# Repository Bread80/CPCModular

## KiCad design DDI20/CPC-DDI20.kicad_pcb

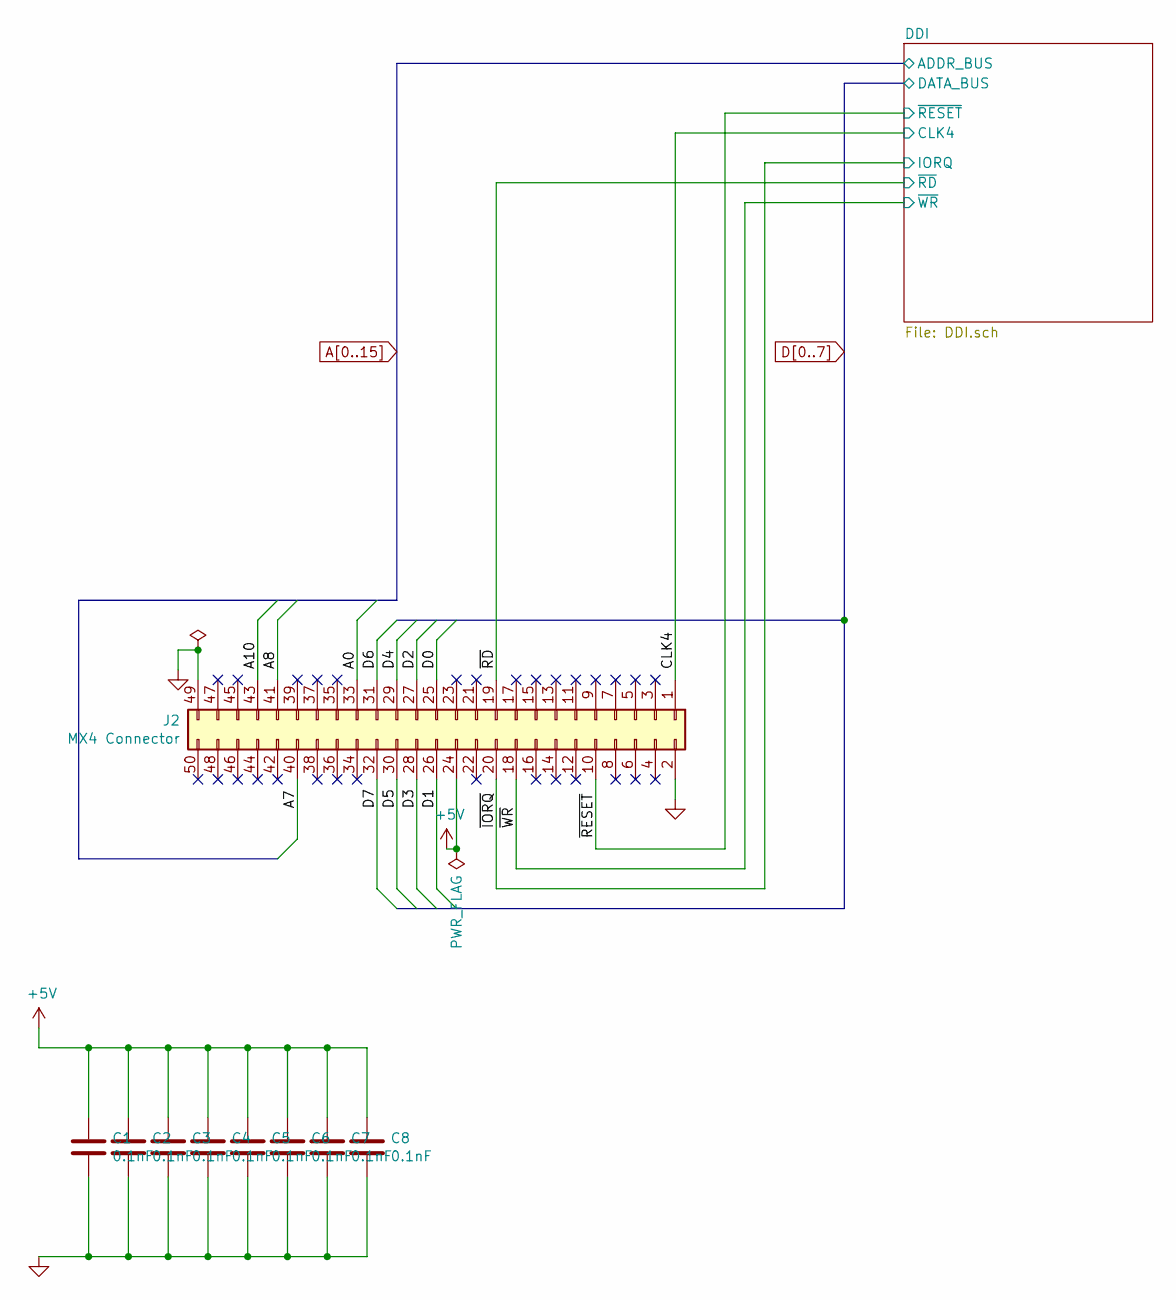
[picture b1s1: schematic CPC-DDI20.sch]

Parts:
C1, C2, C3, C4, C5, C6, C7, C8: 0.1nF; C_Disc_D3.0mm_W2.0mm_P2.50mm
J2: MX4 Connector; IDC-Header_2x25_P2.54mm_Horizontal

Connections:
+5V: C1.1, C2.1, C3.1, C4.1, C5.1, C6.1, C7.1, C8.1, J2.24; also elsewhere on the board
/CLK4: J2.1; also elsewhere on the board
/~IORQ: J2.20; also elsewhere on the board
/~RD: J2.19; also elsewhere on the board
/~RESET: J2.10; also elsewhere on the board
/~WR: J2.18; also elsewhere on the board
A0: J2.33; also elsewhere on the board
A7: J2.40; also elsewhere on the board
A8: J2.41; also elsewhere on the board
A10: J2.43; also elsewhere on the board
D0: J2.25; also elsewhere on the board
D1: J2.26; also elsewhere on the board
D2: J2.27; also elsewhere on the board
D3: J2.28; also elsewhere on the board
D4: J2.29; also elsewhere on the board
D5: J2.30; also elsewhere on the board
D6: J2.31; also elsewhere on the board
D7: J2.32; also elsewhere on the board
GND: C1.2, C2.2, C3.2, C4.2, C5.2, C6.2, C7.2, C8.2, J2.2, J2.49; also elsewhere on the board

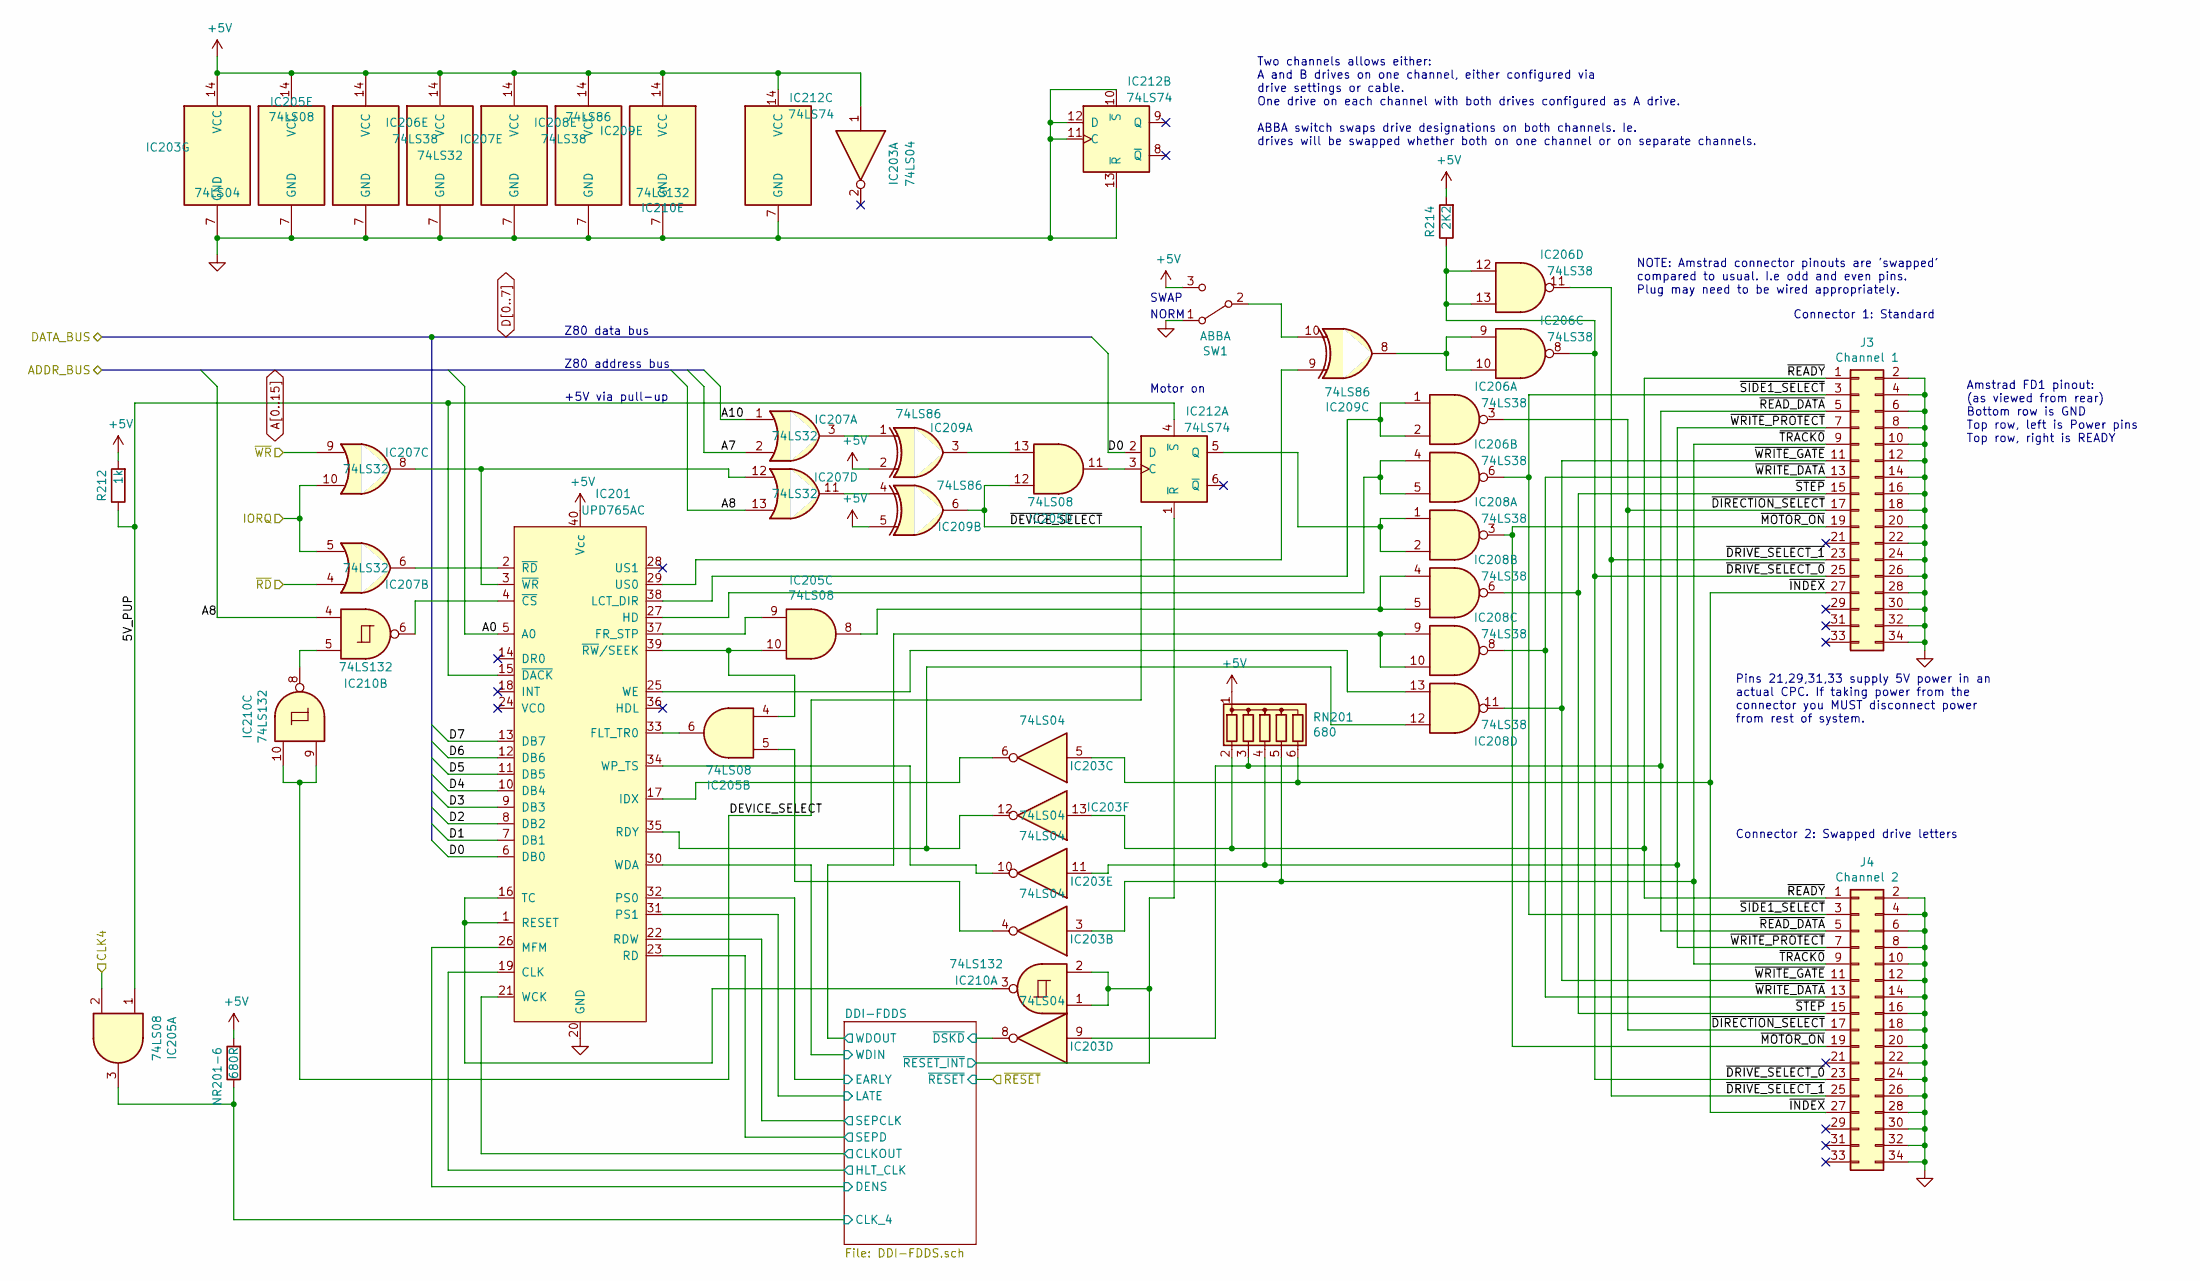
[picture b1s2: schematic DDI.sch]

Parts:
IC201: UPD765AC; DIP-40_W15.24mm_Socket
IC203: 74LS04; DIP-14_W7.62mm_Socket
IC205: 74LS08; DIP-14_W7.62mm_Socket
IC206, IC208: 74LS38; DIP-14_W7.62mm_Socket
IC207: 74LS32; DIP-14_W7.62mm_Socket
IC209: 74LS86; DIP-14_W7.62mm_Socket
IC210: 74LS132; DIP-14_W7.62mm_Socket
IC212: 74LS74; DIP-14_W7.62mm_Socket
J3: Channel 1; IDC-Header_2x17_P2.54mm_Vertical
J4: Channel 2; IDC-Header_2x17_P2.54mm_Vertical
NR201-6: 680R; R_Axial_DIN0207_L6.3mm_D2.5mm_P7.62mm_Horizontal
R212: 1k; R_Axial_DIN0207_L6.3mm_D2.5mm_P7.62mm_Horizontal
R214: 2K2; R_Axial_DIN0207_L6.3mm_D2.5mm_P7.62mm_Horizontal
RN201: 680; R_Array_SIP6
SW1: ABBA; SW_CuK_OS102011MA1QN1_SPDT_Angled

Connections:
+5V: IC201.40 (Vcc), IC203.1, IC203.14 (VCC), IC205.14 (VCC), IC206.14 (VCC), IC207.14 (VCC), IC208.14 (VCC), IC209.2, IC209.5, IC209.14 (VCC), IC210.14 (VCC), IC212.14 (VCC), NR201-6.2, R212.2, R214.2, RN201.1 (common), SW1.3 (C); also elsewhere on the board
/CLK4: IC205.2; also elsewhere on the board
/DDI/5V_PUP: IC201.15 (~DACK), IC205.1, IC212.4 (~S), R212.1
/DDI/DDI-FDDS/CLKOUT: IC201.21 (WCK); also elsewhere on the board
/DDI/DDI-FDDS/CLK_4: IC205.3, NR201-6.1; also elsewhere on the board
/DDI/DDI-FDDS/DENS: IC201.26 (MFM); also elsewhere on the board
/DDI/DDI-FDDS/EARLY: IC201.32 (PS0); also elsewhere on the board
/DDI/DDI-FDDS/HLT_CLK: IC201.19 (CLK); also elsewhere on the board
/DDI/DDI-FDDS/LATE: IC201.31 (PS1); also elsewhere on the board
/DDI/DDI-FDDS/SEPCLK: IC201.22 (RDW); also elsewhere on the board
/DDI/DDI-FDDS/SEPD: IC201.23 (RD); also elsewhere on the board
/DDI/DDI-FDDS/WDIN: IC201.30 (WDA); also elsewhere on the board
/DDI/DDI-FDDS/WDOUT: IC208.9, IC208.10; also elsewhere on the board
/DDI/DDI-FDDS/~DSKD: IC203.8; also elsewhere on the board
/DDI/DDI-FDDS/~RESET_INT: IC210.1, IC210.2, IC212.1 (~R); also elsewhere on the board
/DDI/DEVICE_SELECT: IC205.12, IC209.6, IC210.9, IC210.10
/DDI/~DIRECTION_SELECT: IC206.3, J3.17, J4.17
/DDI/~DRIVE_SELECT_0: IC206.8, IC206.12, IC206.13, J3.25, J4.23, R214.1
/DDI/~DRIVE_SELECT_1: IC206.11, J3.23, J4.25
/DDI/~INDEX: IC203.5, J3.27, J4.27, RN201.6 (R5)
/DDI/~MOTOR_ON: IC208.3, J3.19, J4.19
/DDI/~READY: IC203.13, J3.1, J4.1, RN201.2 (R1)
/DDI/~READ_DATA: IC203.9, J3.5, J4.5, RN201.3 (R2)
/DDI/~SIDE1_SELECT: IC206.6, J3.3, J4.3
/DDI/~STEP: IC208.6, J3.15, J4.15
/DDI/~TRACK0: IC203.3, J3.9, J4.9, RN201.5 (R4)
/DDI/~WRITE_DATA: IC208.8, J3.13, J4.13
/DDI/~WRITE_GATE: IC208.11, J3.11, J4.11
/DDI/~WRITE_PROTECT: IC203.11, J3.7, J4.7, RN201.4 (R3)
/~IORQ: IC207.5, IC207.10; also elsewhere on the board
/~RD: IC207.4; also elsewhere on the board
/~WR: IC207.9; also elsewhere on the board
A0: IC201.5 (A0); also elsewhere on the board
A7: IC207.2; also elsewhere on the board
A8: IC207.13, IC210.4; also elsewhere on the board
A10: IC207.1; also elsewhere on the board
D0: IC201.6 (DB0), IC212.2 (D); also elsewhere on the board
D1: IC201.7 (DB1); also elsewhere on the board
D2: IC201.8 (DB2); also elsewhere on the board
D3: IC201.9 (DB3); also elsewhere on the board
D4: IC201.10 (DB4); also elsewhere on the board
D5: IC201.11 (DB5); also elsewhere on the board
D6: IC201.12 (DB6); also elsewhere on the board
D7: IC201.13 (DB7); also elsewhere on the board
GND: IC201.20 (GND), IC203.7 (GND), IC205.7 (GND), IC206.7 (GND), IC207.7 (GND), IC208.7 (GND), IC209.7 (GND), IC210.7 (GND), IC212.7 (GND), IC212.10 (~S), IC212.11 (C), IC212.12 (D), IC212.13 (~R), J3.2, J3.4, J3.6, J3.8, J3.10, J3.12, J3.14, J3.16, J3.18, J3.20, J3.22, J3.24, J3.26, J3.28, J3.30, J3.32, J3.34, J4.2, J4.4, J4.6, J4.8, J4.10, J4.12, J4.14, J4.16, J4.18, J4.20, J4.22, J4.24, J4.26, J4.28, J4.30, J4.32, J4.34, SW1.1 (A); also elsewhere on the board
unnamed: IC201.1 (RESET), IC201.16 (TC), IC210.3
unnamed: IC201.2 (~RD), IC207.6
unnamed: IC201.3 (~WR), IC207.8, IC207.12
unnamed: IC201.4 (~CS), IC210.6
unnamed: IC201.17 (IDX), IC203.6
unnamed: IC201.25 (WE), IC208.13
unnamed: IC201.27 (HD), IC206.4, IC206.5
unnamed: IC201.29 (US0), IC209.9
unnamed: IC201.33 (FLT_TR0), IC205.6
unnamed: IC201.34 (WP_TS), IC203.10
unnamed: IC201.35 (RDY), IC203.12, IC208.12
unnamed: IC201.37 (FR_STP), IC205.9
unnamed: IC201.38 (LCT_DIR), IC206.1, IC206.2
unnamed: IC201.39 (~RW~/SEEK), IC205.4, IC205.10
unnamed: IC203.4, IC205.5
unnamed: IC205.8, IC208.4, IC208.5
unnamed: IC205.11, IC212.3 (C)
unnamed: IC205.13, IC209.3
unnamed: IC206.9, IC206.10, IC209.8
unnamed: IC207.3, IC209.1
unnamed: IC207.11, IC209.4
unnamed: IC208.1, IC208.2, IC212.5 (Q)
unnamed: IC209.10, SW1.2 (B)
unnamed: IC210.5, IC210.8

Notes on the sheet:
Motor on
Z80 data bus
Z80 address bus
+5V via pull-up
Pins 21,29,31,33 supply 5V power in an actual CPC. If taking power from the connector you MUST disconnect power from rest of system.
Connector 1: Standard
Connector 2: Swapped drive letters
NORM
SWAP
Two channels allows either: A and B drives on one channel, either configured via drive settings or cable. One drive on each channel with both drives configured as A drive. ABBA switch swaps drive designations on both channels. Ie. drives will be swapped whether both on one channel or on separate ch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
NOTE: Amstrad connector pinouts are 'swapped' compared to usual. I.e odd and even pins. Plug may need to be wired appropriately.
Amstrad FD1 pinout: (as viewed from rear) Bottom row is GND Top row, left is Power pins Top row, right is READY

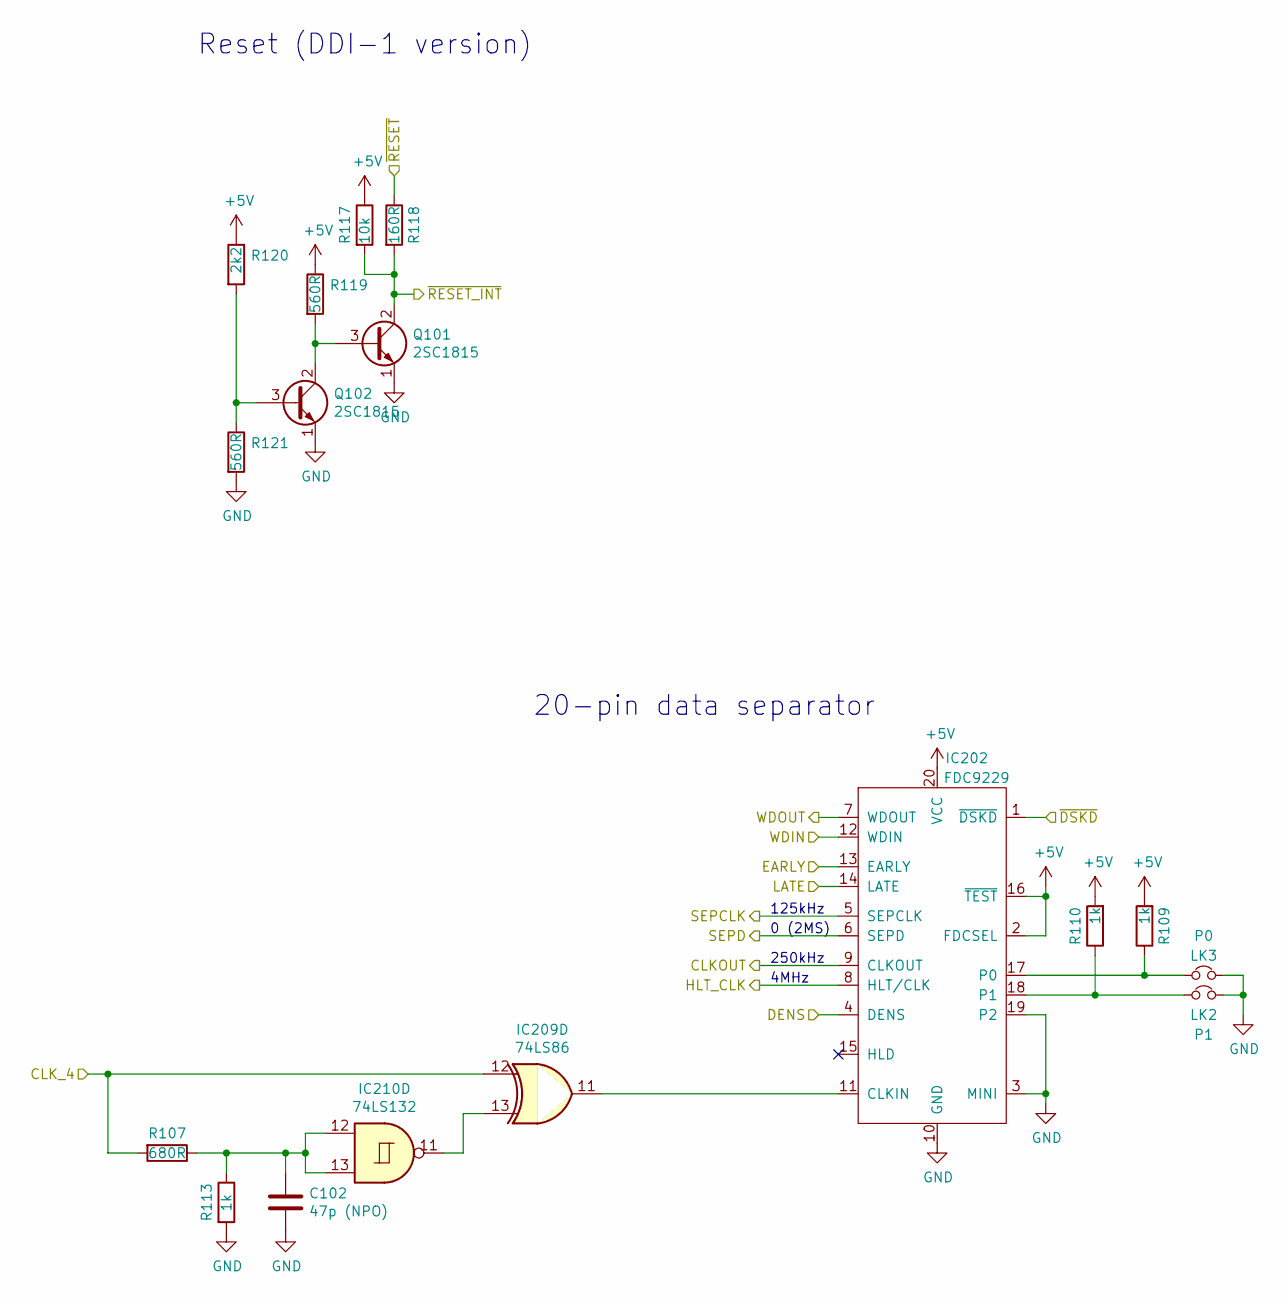
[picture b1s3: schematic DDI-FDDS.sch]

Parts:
C102: 47p (NPO); C_Disc_D3.0mm_W2.0mm_P2.50mm
IC202: FDC9229; DIP-20_W7.62mm_Socket
IC209: 74LS86; DIP-14_W7.62mm_Socket
IC210: 74LS132; DIP-14_W7.62mm_Socket
LK2: P1; SolderJumper-2_P1.3mm_Bridged_RoundedPad1.0x1.5mm
LK3: P0; SolderJumper-2_P1.3mm_Bridged_RoundedPad1.0x1.5mm
Q101, Q102: 2SC1815; TO-92_HandSolder
R107: 680R; R_Axial_DIN0207_L6.3mm_D2.5mm_P7.62mm_Horizontal
R109, R110, R113: 1k; R_Axial_DIN0207_L6.3mm_D2.5mm_P7.62mm_Horizontal
R117: 10k; R_Axial_DIN0207_L6.3mm_D2.5mm_P7.62mm_Horizontal
R118: 160R; R_Axial_DIN0207_L6.3mm_D2.5mm_P7.62mm_Horizontal
R119, R121: 560R; R_Axial_DIN0207_L6.3mm_D2.5mm_P7.62mm_Horizontal
R120: 2k2; R_Axial_DIN0207_L6.3mm_D2.5mm_P7.62mm_Horizontal

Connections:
+5V: IC202.2 (FDCSEL), IC202.16 (~TEST), IC202.20 (VCC), R109.2, R110.2, R117.1, R119.1, R120.1; also elsewhere on the board
/DDI/DDI-FDDS/CLKOUT: IC202.9 (CLKOUT); also elsewhere on the board
/DDI/DDI-FDDS/CLK_4: IC209.12, R107.2; also elsewhere on the board
/DDI/DDI-FDDS/DENS: IC202.4 (DENS); also elsewhere on the board
/DDI/DDI-FDDS/EARLY: IC202.13 (EARLY); also elsewhere on the board
/DDI/DDI-FDDS/HLT_CLK: IC202.8 (HLT/CLK); also elsewhere on the board
/DDI/DDI-FDDS/LATE: IC202.14 (LATE); also elsewhere on the board
/DDI/DDI-FDDS/SEPCLK: IC202.5 (SEPCLK); also elsewhere on the board
/DDI/DDI-FDDS/SEPD: IC202.6 (SEPD); also elsewhere on the board
/DDI/DDI-FDDS/WDIN: IC202.12 (WDIN); also elsewhere on the board
/DDI/DDI-FDDS/WDOUT: IC202.7 (WDOUT); also elsewhere on the board
/DDI/DDI-FDDS/~DSKD: IC202.1 (~DSKD); also elsewhere on the board
/DDI/DDI-FDDS/~RESET_INT: Q101.2 (C), R117.2, R118.2; also elsewhere on the board
/~RESET: R118.1; also elsewhere on the board
GND: C102.2, IC202.3 (MINI), IC202.10 (GND), IC202.19 (P2), LK2.2, LK3.2, Q101.1 (E), Q102.1 (E), R113.2, R121.2; also elsewhere on the board
unnamed: C102.1, IC210.12, IC210.13, R107.1, R113.1
unnamed: IC202.11 (CLKIN), IC209.11
unnamed: IC202.17 (P0), LK3.1, R109.1
unnamed: IC202.18 (P1), LK2.1, R110.1
unnamed: IC209.13, IC210.11
unnamed: Q101.3 (B), Q102.2 (C), R119.2
unnamed: Q102.3 (B), R120.2, R121.1

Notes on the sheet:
4MHz
250kHz
0 (2MS)
125kHz
20-pin data separator
Reset (DDI-1 version)

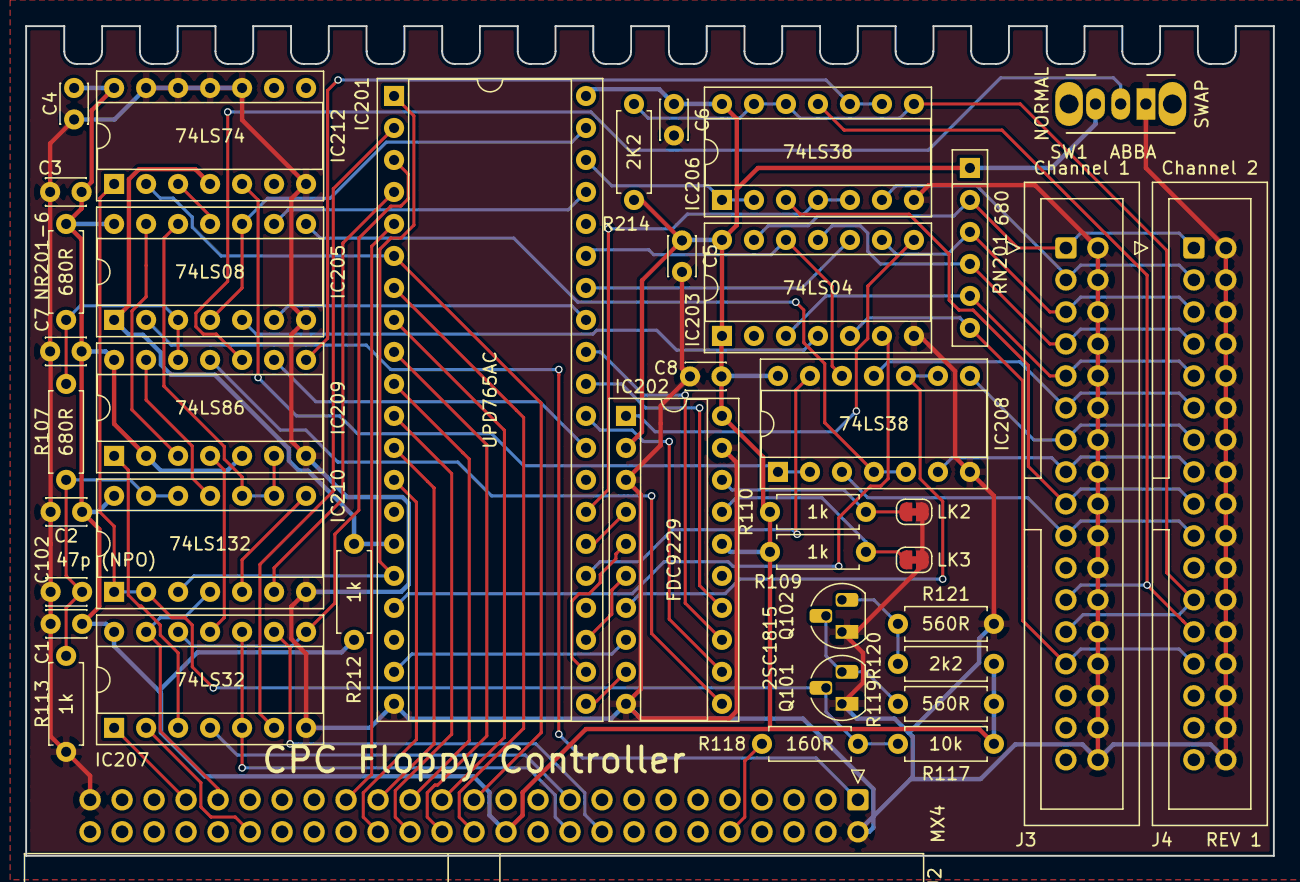
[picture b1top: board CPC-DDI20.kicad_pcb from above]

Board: 2 copper layers, 99.1 x 65.9 mm, 40 parts (0 on the bottom side), 77 nets.

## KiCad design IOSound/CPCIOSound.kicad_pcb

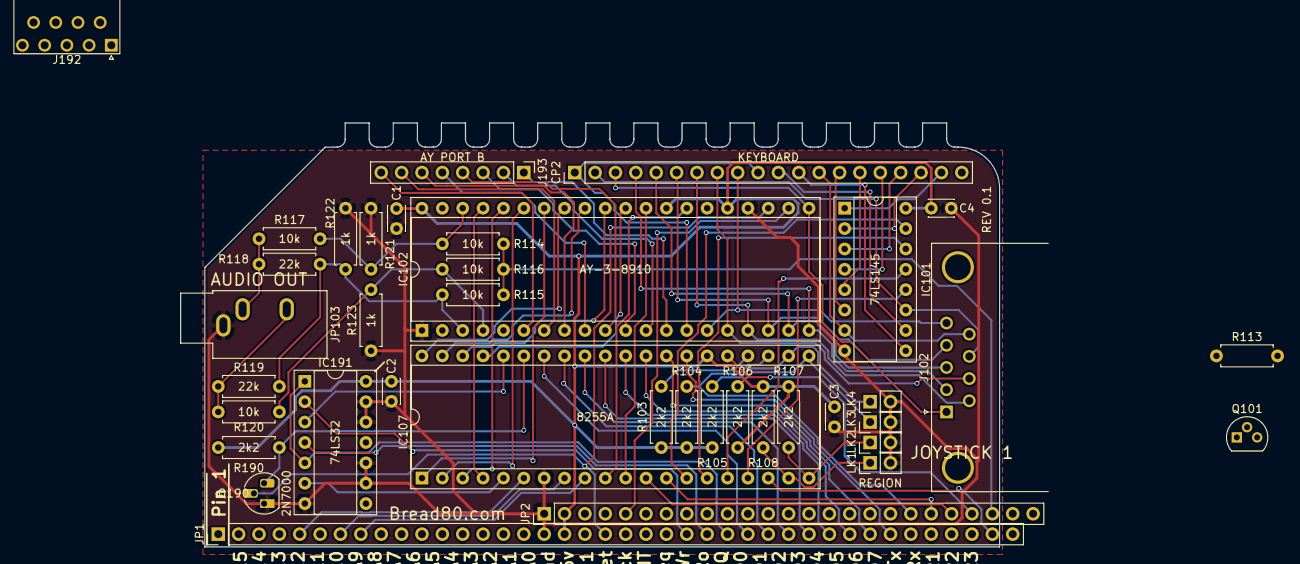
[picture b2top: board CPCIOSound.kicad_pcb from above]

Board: 2 copper layers, 99.1 x 52.9 mm, 39 parts (0 on the bottom side), 78 nets.

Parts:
C1, C2, C3, C4: 0.1nF; C_Disc_D3.0mm_W2.0mm_P2.50mm
CP2: Keyboard Connector (20-way inline 2.54mm); PinHeader_1x20_P2.54mm_Vertical
IC101: 74LS145; DIP-16_W7.62mm_Socket
IC102: AY-3-8910; DIP-40_W15.24mm_Socket
IC107: 8255A; DIP-40_W15.24mm_Socket
IC191: 74LS32; DIP-14_W7.62mm_Socket
J102: Paddle Port (9-Pin D); DSUB-9_Male_Horizontal_P2.77x2.84mm_EdgePinOffset9.90mm_Hou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
J192: Paddle Port 2 (9-Pin D); DSUB-9_Male_Horizontal_P2.77x2.84mm_EdgePinOffset9.40mm
J193: Conn_01x08_Male; PinHeader_1x08_P2.54mm_Vertical
JP1: RC2014Bus; PinHeader_1x40_P2.54mm_Vertical
JP2: RC2014ExtendedBus; PinHeader_1x25_P2.54mm_Vertical
JP103: Stereo Sound Connector (3.5mm jack); Jack_3.5mm_CUI_SJ1-3533NG_Horizontal
LK1, LK2, LK3, LK4: Jumper_NO_Small; PinHeader_1x02_P2.54mm_Vertical
Q101: 2SC2120; TO-92L
Q190: 2N7000; TO-92_HandSolder
R103, R104, R105, R106, R107, R108, R190: 2k2; R_Axial_DIN0207_L6.3mm_D2.5mm_P7.62mm_Horizontal
R113, R121, R122, R123: 1k; R_Axial_DIN0207_L6.3mm_D2.5mm_P7.62mm_Horizontal
R114, R115, R116, R117, R120: 10k; R_Axial_DIN0207_L6.3mm_D2.5mm_P7.62mm_Horizontal
R118, R119: 22k; R_Axial_DIN0207_L6.3mm_D2.5mm_P7.62mm_Horizontal

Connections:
+5V: C1.1, C2.1, C3.1, C4.1, IC101.16, IC102.25, IC102.28, IC102.40, IC107.26, IC191.14, JP1.18, JP2.2, R103.1, R104.1, R105.1, R106.1, R107.1, R108.1, R190.1
/IO_SOUND/A: IC102.4, R116.1, R120.2, R123.2
/IO_SOUND/AYA0: CP2.3, IC102.21, J102.1, J192.1
/IO_SOUND/AYA1: CP2.4, IC102.20, J102.2, J192.2
/IO_SOUND/AYA2: CP2.5, IC102.19, J102.3, J192.3
/IO_SOUND/AYA3: CP2.6, IC102.18, J102.4, J192.4
/IO_SOUND/AYA4: CP2.7, IC102.17, J102.6, J192.5
/IO_SOUND/AYA5: CP2.8, IC102.16, J102.7, J192.6
/IO_SOUND/AYA6: CP2.9, IC102.15, J102.5, J192.7
/IO_SOUND/AYA7: CP2.1, CP2.10, IC102.14
/IO_SOUND/B: IC102.3, R115.1, R118.2, R119.2, R122.2
/IO_SOUND/C: IC102.38, R114.1, R117.2, R121.2
/IO_SOUND/CAS_RD_DATA: IC107.25, JP2.22
/IO_SOUND/CAS_WR_DATA: IC107.12, JP2.21
/IO_SOUND/COMMON: CP2.2, IC101.11, J102.8, J192.9
/IO_SOUND/COM_2: CP2.13, IC101.7, J102.9, J192.8
/IO_SOUND/PA0: IC102.37, IC107.4
/IO_SOUND/PA1: IC102.36, IC107.3
/IO_SOUND/PA2: IC102.35, IC107.2
/IO_SOUND/PA3: IC102.34, IC107.1
/IO_SOUND/PA4: IC102.33, IC107.40
/IO_SOUND/PA5: IC102.32, IC107.39
/IO_SOUND/PA6: IC102.31, IC107.38
/IO_SOUND/PA7: IC102.30, IC107.37
/IO_SOUND/PC0: IC101.15, IC107.14
/IO_SOUND/PC1: IC101.14, IC107.15
/IO_SOUND/PC2: IC101.13, IC107.16
/IO_SOUND/PC3: IC101.12, IC107.17
/IO_SOUND/SOUND: JP2.23, R114.2, R115.2, R116.2
/IO_SOUND/SOUND_CLK: IC102.22, JP2.5
/IO_SOUND/VSYNC: IC107.18, JP1.39
/IO_SOUND/Y1: CP2.19, IC101.1
/IO_SOUND/Y2: CP2.18, IC101.2
/IO_SOUND/Y3: CP2.17, IC101.3
/IO_SOUND/Y4: CP2.16, IC101.4
/IO_SOUND/Y5: CP2.15, IC101.5
/IO_SOUND/Y6: CP2.14, IC101.6
/IO_SOUND/Y8: CP2.12, IC101.9
/IO_SOUND/Y9: CP2.11, IC101.10
/IO_SOUND/~CAS_MOTOR: IC107.13, JP2.20, R113.1
/IO_SOUND/~EXP: IC107.23, JP2.19, R104.2
/IO_SOUND/~IORQ: IC191.1, IC191.5, JP1.26
/IO_SOUND/~RD: IC191.4, JP1.25
/IO_SOUND/~RESET: IC102.23, JP1.20, Q190.2
/IO_SOUND/~WR: IC191.2, JP1.24
A8: IC107.9, JP1.8
A9: IC107.8, JP1.7
A11: IC107.6, JP1.5
D0: IC107.34, JP1.27
D1: IC107.33, JP1.28
D2: IC107.32, JP1.29
D3: IC107.31, JP1.30
D4: IC107.30, JP1.31
D5: IC107.29, JP1.32
D6: IC107.28, JP1.33
D7: IC107.27, JP1.34
GND: C1.2, C2.2, C3.2, C4.2, IC101.8, IC102.1, IC102.24, IC107.7, IC191.7, IC191.9, IC191.10, IC191.12, IC191.13, JP1.17, JP2.1, JP103.S, LK1.2, LK2.2, LK3.2, LK4.2, Q101.1, Q190.1, R121.1, R122.1, R123.1
unnamed: IC102.6, J193.8
unnamed: IC102.7, J193.7
unnamed: IC102.8, J193.6
unnamed: IC102.9, J193.5
unnamed: IC102.10, J193.4
unnamed: IC102.11, J193.3
unnamed: IC102.12, J193.2
unnamed: IC102.13, J193.1
unnamed: IC102.27, IC107.10
unnamed: IC102.29, IC107.11
unnamed: IC107.5, IC191.6
unnamed: IC107.19, LK1.1, R108.2
unnamed: IC107.20, LK2.1, R107.2
unnamed: IC107.21, LK3.1, R106.2
unnamed: IC107.22, LK4.1, R105.2
unnamed: IC107.24, R103.2
unnamed: IC107.35, Q190.3, R190.2
unnamed: IC107.36, IC191.3
unnamed: JP103.R, R119.1, R120.1
unnamed: JP103.T, R117.1, R118.1
unnamed: Q101.2, R113.2

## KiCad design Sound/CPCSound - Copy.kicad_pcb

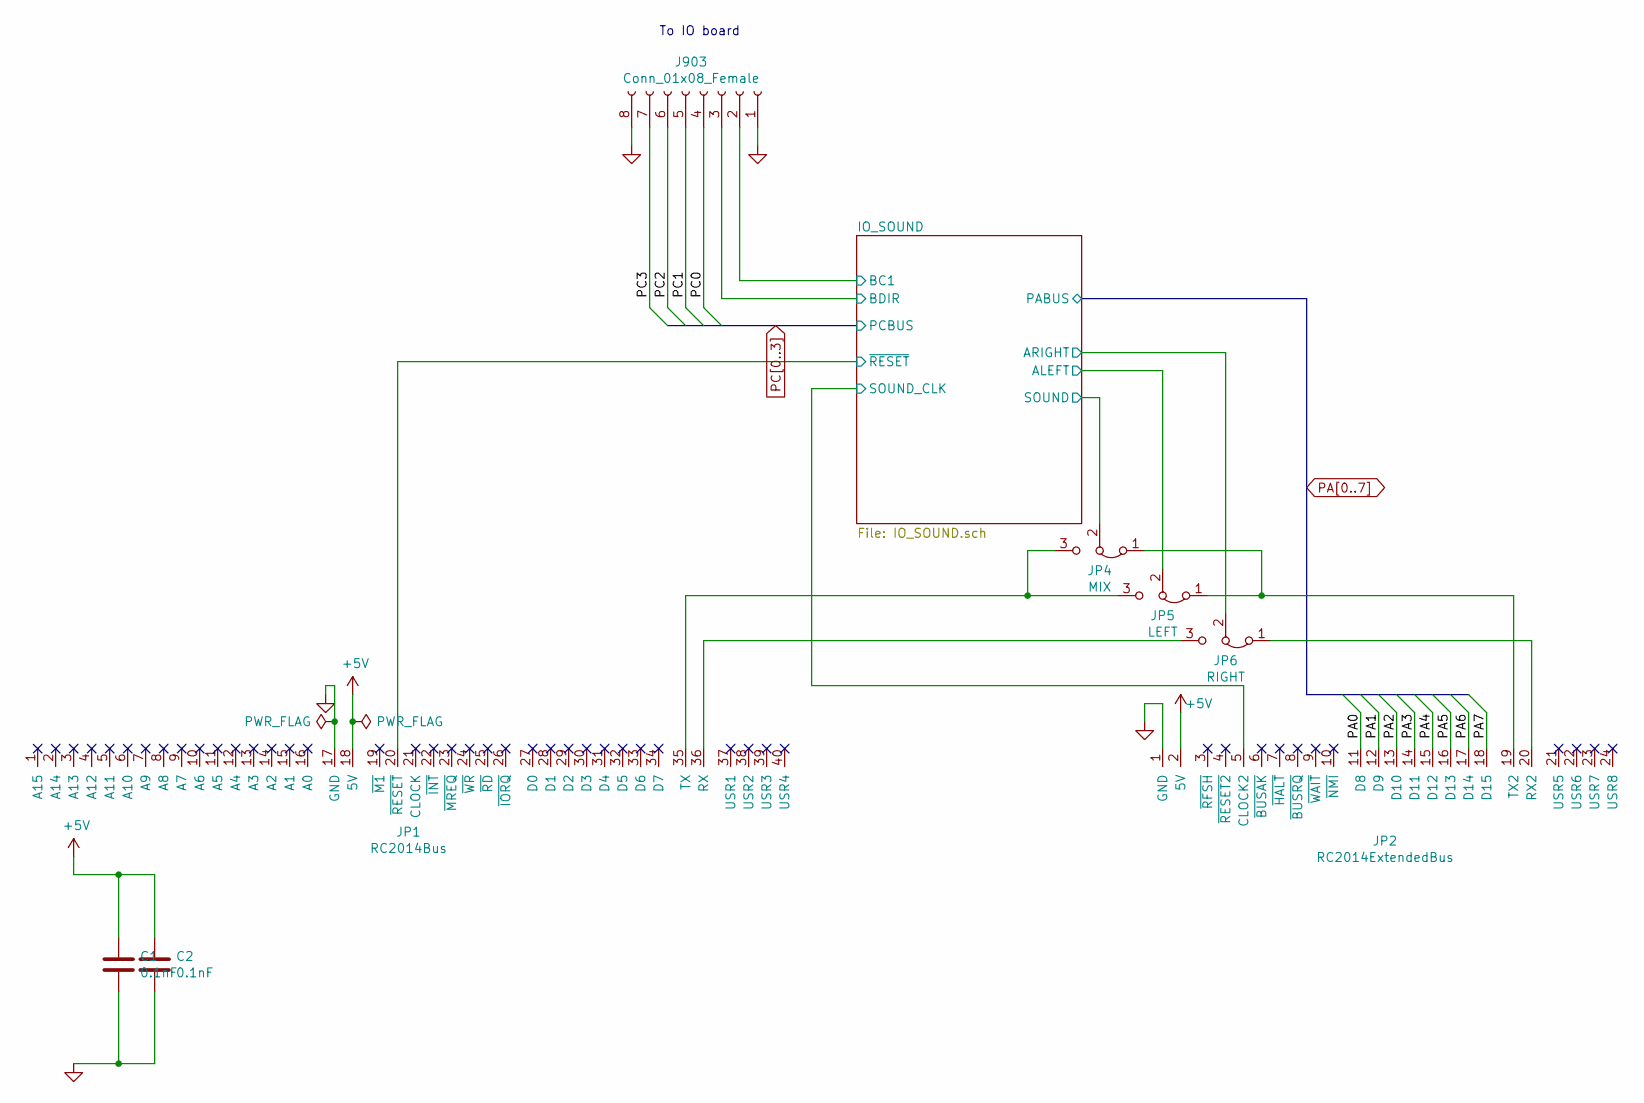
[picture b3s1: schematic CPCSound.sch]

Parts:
C1, C2: 0.1nF; C_Disc_D3.0mm_W2.0mm_P2.50mm
J903: Conn_01x08_Female; PinSocket_1x08_P2.54mm_Vertical
JP1: RC2014Bus; PinHeader_1x40_P2.54mm_Vertical
JP2: RC2014ExtendedBus; PinHeader_1x25_P2.54mm_Vertical
JP4: MIX; PinHeader_1x03_P2.54mm_Vertical
JP5: LEFT; PinHeader_1x03_P2.54mm_Vertical
JP6: RIGHT; PinHeader_1x03_P2.54mm_Vertical

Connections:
+5V: C1.1, C2.1, JP1.18 (5V), JP2.2 (5V); also elsewhere on the board
/IO_SOUND/ALEFT: JP5.2 (C); also elsewhere on the board
/IO_SOUND/ARIGHT: JP6.2 (C); also elsewhere on the board
/IO_SOUND/BC1: J903.2; also elsewhere on the board
/IO_SOUND/BDIR: J903.3; also elsewhere on the board
/IO_SOUND/SOUND: JP4.2 (C); also elsewhere on the board
/IO_SOUND/SOUND_CLK: JP2.5 (CLOCK2); also elsewhere on the board
/IO_SOUND/~RESET: JP1.20 (~RESET); also elsewhere on the board
GND: C1.2, C2.2, J903.1, J903.8, JP1.17 (GND), JP2.1 (GND); also elsewhere on the board
unnamed: JP1.35 (TX), JP4.3 (B), JP5.3 (B)
unnamed: JP1.36 (RX), JP6.3 (B)
unnamed: JP2.19 (TX2), JP4.1 (A), JP5.1 (A)
unnamed: JP2.20 (RX2), JP6.1 (A)
PA0: JP2.11 (D8); also elsewhere on the board
PA1: JP2.12 (D9); also elsewhere on the board
PA2: JP2.13 (D10); also elsewhere on the board
PA3: JP2.14 (D11); also elsewhere on the board
PA4: JP2.15 (D12); also elsewhere on the board
PA5: JP2.16 (D13); also elsewhere on the board
PA6: JP2.17 (D14); also elsewhere on the board
PA7: JP2.18 (D15); also elsewhere on the board
PC0: J903.4; also elsewhere on the board
PC1: J903.5; also elsewhere on the board
PC2: J903.6; also elsewhere on the board
PC3: J903.7; also elsewhere on the board

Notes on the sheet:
To IO board

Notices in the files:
DDI20/CPC-DDI20.kicad_pcb:
© Mike Sutton - Bread80.com
IOSound/CPCIOSound.kicad_pcb:
© Mike Sutton 2022
VideoR1Backup/CPCVideo.kicad_pcb:
© Mike Sutton, 2024
